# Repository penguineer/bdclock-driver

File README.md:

# Bulbdial Clock Driver board

> Driver Board for the bulbdial clock in [Netz39](https://www.netz39.de)

This is a driver board for the bulbdial clock built by [Yomin](https://github.com/Yomin) in [bdclock](https://github.com/Yomin/bdclock), which is in turn inspired by the bulbdial clock developed at [Evil Mad Scientist Laboratories](https://www.evilmadscientist.com/2009/a-bulbdial-clock/).

## Interface

The driver circuit operates independently and only needs to be fed data when the displayed values should change.

### Input

The circuit has three input controls `DATA`, `CLK` and `COMMIT`.

The data set contains of 3x8 data bits encoding the active LED for each of the three rows (where the order depends on how the rows are connected and only 0 to 11 lead to an illmuniated LED). Any number of bits can be sent, but only the last 24 bits will be stored in the registers.

The `DATA` is stored on the positive `CLK` edge. When all bits are loaded, the actual content is made visible to the drivers with a positive edge on `COMMIT`. For convenience, `CLK` and `COMMIT` can be driven together. In this case, the shift register's content is always one clock ahead of the storage register (see [SN74HC595 datasheet](https://www.ti.com/lit/ds/symlink/sn74hc595.pdf) p. 11).

### Output

The multiplexer is driven by an internal clock generater.

Each clock row is expected to have a common cathode, which will be multiplexed at the set switching frequency.

The line decoder selects one out of 12 LEDs to be active and expects the anodes of the clock LEDs to be connected to the matching output.

To switch a row off, select a value between 12 and 255, as these are ignored. The row will still be part of the multiplexing cycle.

## License

[MIT](LICENSE.txt) © 2023 Stefan Haun and contributors

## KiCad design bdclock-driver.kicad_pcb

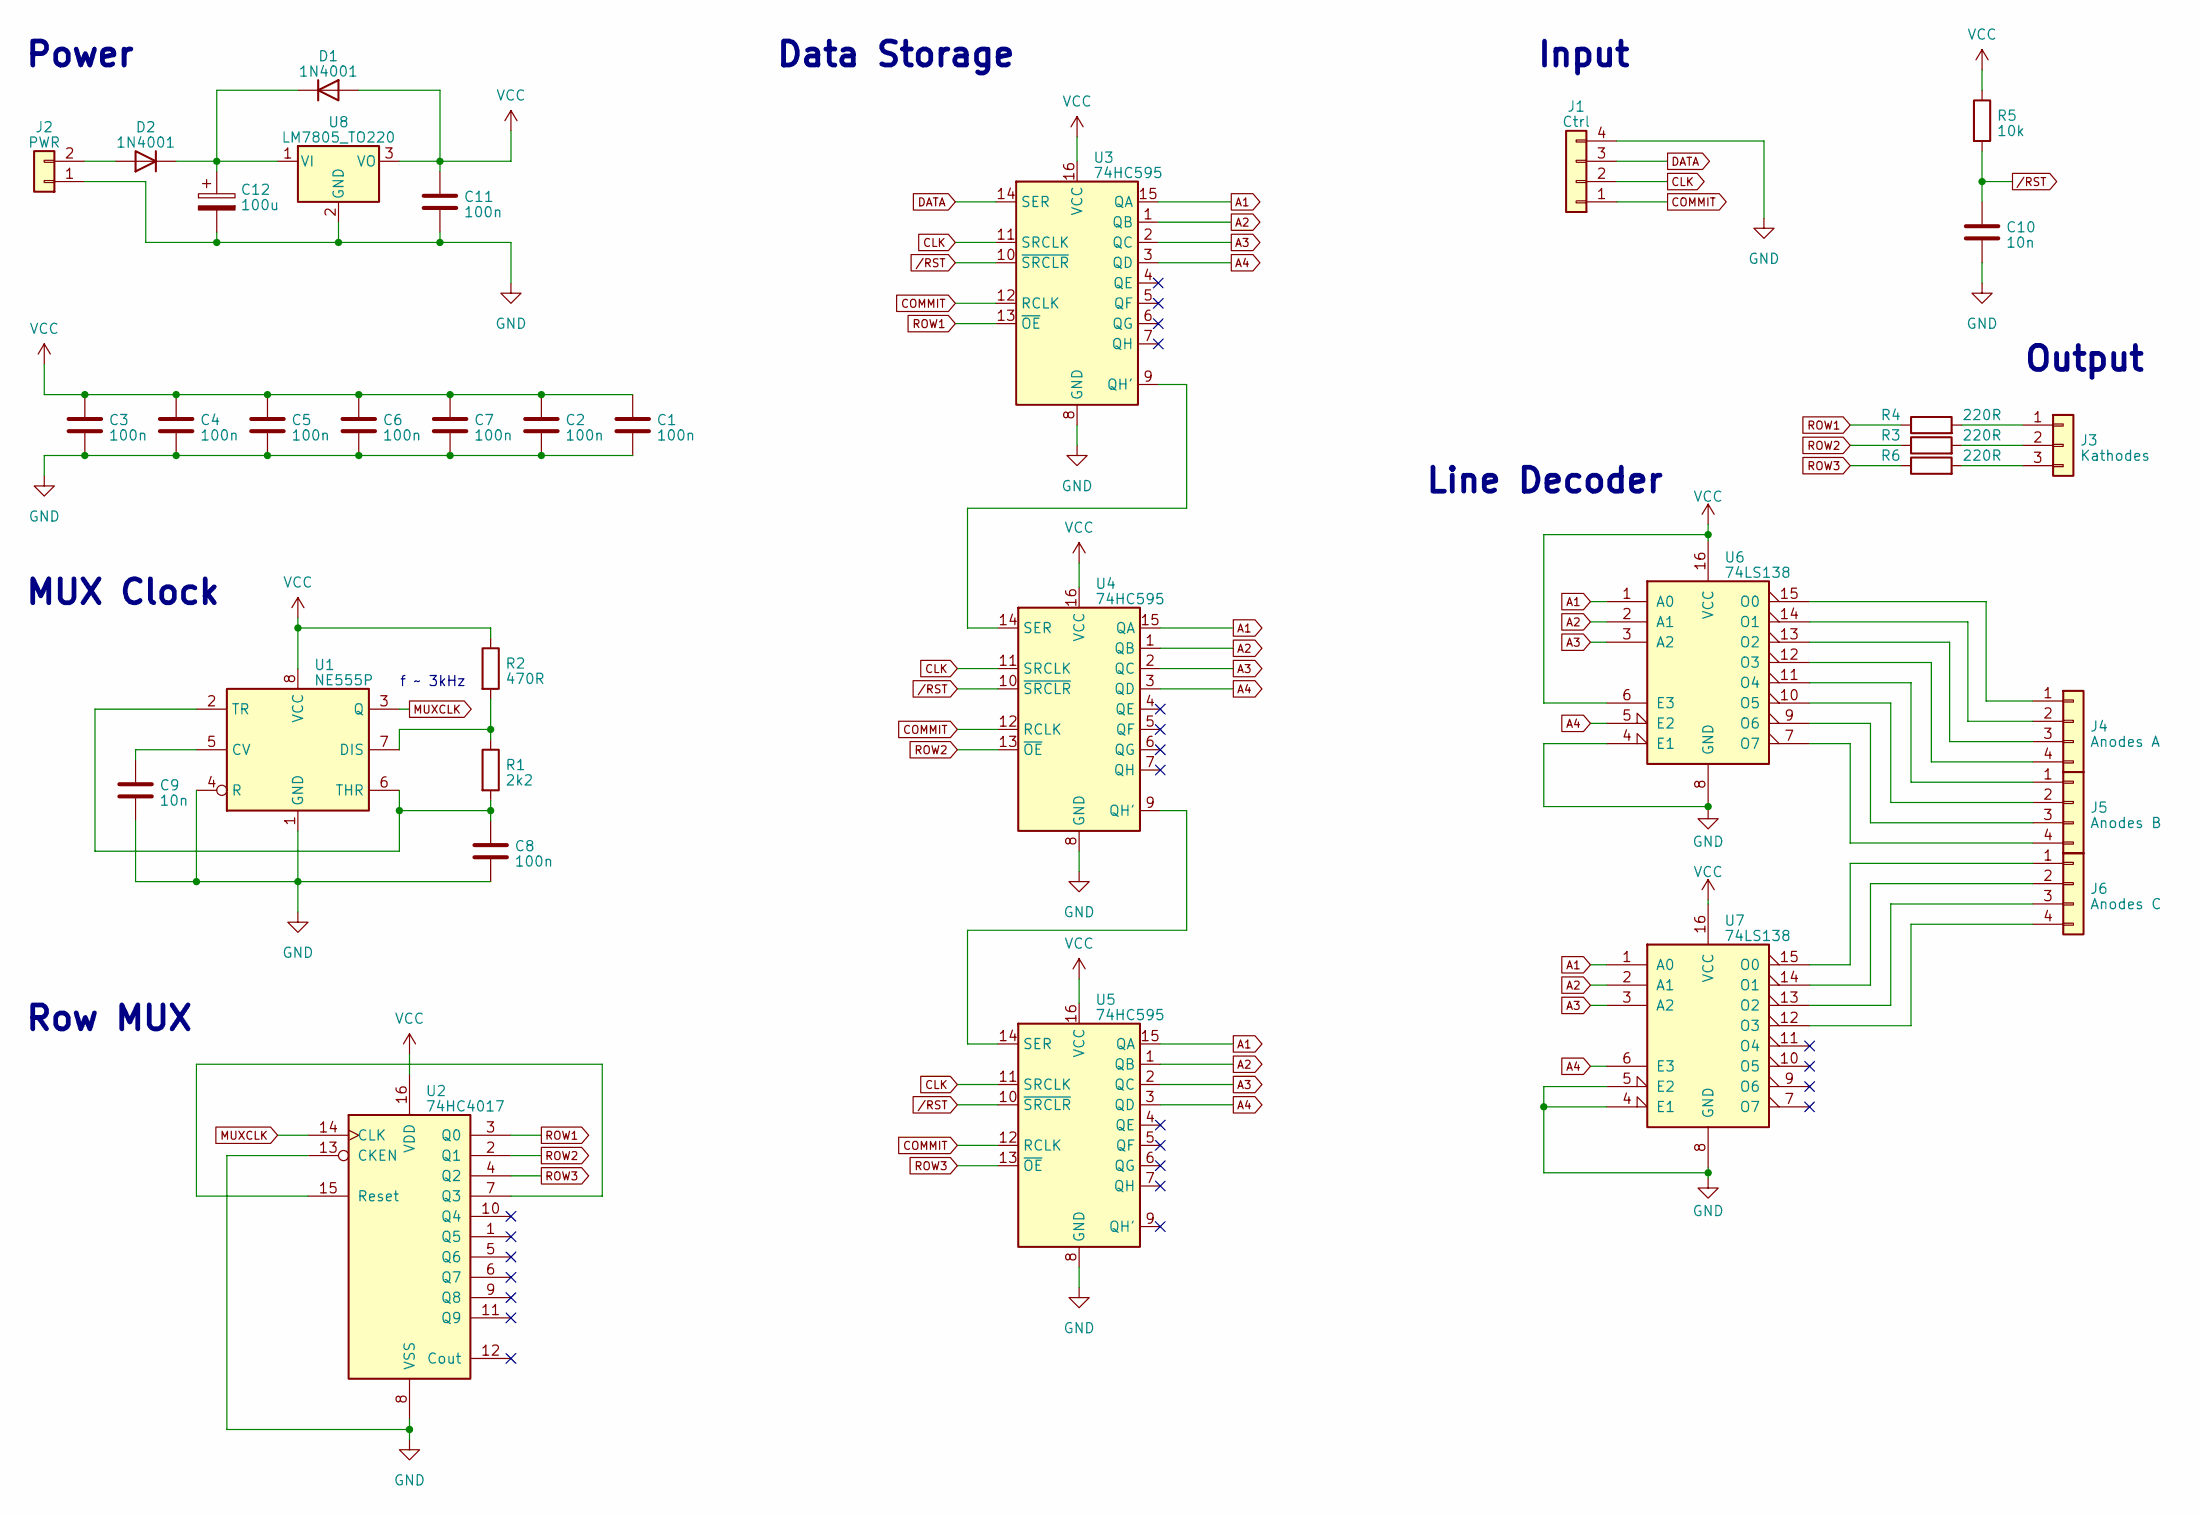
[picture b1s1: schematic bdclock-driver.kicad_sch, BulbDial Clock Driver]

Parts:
C1, C2, C3, C4, C5, C6, C7, C8, C11: 100n; C_Disc_D4.3mm_W1.9mm_P5.00mm
C9, C10: 10n; C_Disc_D4.3mm_W1.9mm_P5.00mm
C12: 100u; CP_Radial_D6.3mm_P2.50mm
D1, D2: 1N4001; D_DO-41_SOD81_P10.16mm_Horizontal
J1: Ctrl; PinSocket_1x04_P2.54mm_Vertical
J2: PWR; TerminalBlock_Altech_AK300-2_P5.00mm
J3: Kathodes; TerminalBlock_Altech_AK300-3_P5.00mm
J4: Anodes A; TerminalBlock_Altech_AK300-4_P5.00mm
J5: Anodes B; TerminalBlock_Altech_AK300-4_P5.00mm
J6: Anodes C; TerminalBlock_Altech_AK300-4_P5.00mm
R1: 2k2; R_Axial_DIN0207_L6.3mm_D2.5mm_P7.62mm_Horizontal
R2: 470R; R_Axial_DIN0207_L6.3mm_D2.5mm_P7.62mm_Horizontal
R3, R4, R6: 220R; R_Axial_DIN0207_L6.3mm_D2.5mm_P7.62mm_Horizontal
R5: 10k; R_Axial_DIN0207_L6.3mm_D2.5mm_P7.62mm_Horizontal
U1: NE555P; DIP-8_W7.62mm_Socket_LongPads
U2: 74HC4017; DIP-16_W7.62mm_Socket_LongPads
U3, U4, U5: 74HC595; DIP-16_W7.62mm_Socket_LongPads
U6, U7: 74LS138; DIP-16_W7.62mm_Socket_LongPads
U8: LM7805_TO220; TO-220-3_Vertical

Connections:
A1: U3.15 (QA), U4.15 (QA), U5.15 (QA), U6.1 (A0), U7.1 (A0)
A2: U3.1 (QB), U4.1 (QB), U5.1 (QB), U6.2 (A1), U7.2 (A1)
A3: U3.2 (QC), U4.2 (QC), U5.2 (QC), U6.3 (A2), U7.3 (A2)
A4: U3.3 (QD), U4.3 (QD), U5.3 (QD), U6.5 (E2), U7.6 (E3)
CLK: J1.2, U3.11 (SRCLK), U4.11 (SRCLK), U5.11 (SRCLK)
COMMIT: J1.1, U3.12 (RCLK), U4.12 (RCLK), U5.12 (RCLK)
DATA: J1.3, U3.14 (SER)
GND: C1.2, C2.2, C3.2, C4.2, C5.2, C6.2, C7.2, C8.2, C9.2, C10.2, C11.2, C12.2, J1.4, J2.1, U1.1 (GND), U1.4 (R), U2.8 (VSS), U2.13 (CKEN), U3.8 (GND), U4.8 (GND), U5.8 (GND), U6.4 (E1), U6.8 (GND), U7.4 (E1), U7.5 (E2), U7.8 (GND), U8.2 (GND)
MUXCLK: U1.3 (Q), U2.14 (CLK)
unnamed: C12.1, D1.1 (K), D2.1 (K), U8.1 (VI)
unnamed: D2.2 (A), J2.2
unnamed: J3.1, R4.2
unnamed: J3.2, R3.2
unnamed: J3.3, R6.2
unnamed: J4.1, U6.15 (O0)
unnamed: J4.2, U6.14 (O1)
unnamed: J4.3, U6.13 (O2)
unnamed: J4.4, U6.12 (O3)
unnamed: J5.1, U6.11 (O4)
unnamed: J5.2, U6.10 (O5)
unnamed: J5.3, U6.9 (O6)
unnamed: J5.4, U6.7 (O7)
unnamed: J6.1, U7.15 (O0)
unnamed: J6.2, U7.14 (O1)
unnamed: J6.3, U7.13 (O2)
unnamed: J6.4, U7.12 (O3)
unnamed: C9.1, U1.5 (CV)
unnamed: R1.1, R2.2, U1.7 (DIS)
unnamed: C8.1, R1.2, U1.2 (TR), U1.6 (THR)
unnamed: U2.7 (Q3), U2.15 (Reset)
unnamed: U3.9 (QH'), U4.14 (SER)
unnamed: U4.9 (QH'), U5.14 (SER)
ROW1: R4.1, U2.3 (Q0), U3.13 (~OE)
ROW2: R3.1, U2.2 (Q1), U4.13 (~OE)
ROW3: R6.1, U2.4 (Q2), U5.13 (~OE)
VCC: C1.1, C2.1, C3.1, C4.1, C5.1, C6.1, C7.1, C11.1, D1.2 (A), R2.1, R5.1, U1.8 (VCC), U2.16 (VDD), U3.16 (VCC), U4.16 (VCC), U5.16 (VCC), U6.6 (E3), U6.16 (VCC), U7.16 (VCC), U8.3 (VO)
/RST: C10.1, R5.2, U3.10 (~SRCLR), U4.10 (~SRCLR), U5.10 (~SRCLR)

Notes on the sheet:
MUX Clock
Row MUX
Input
Line Decoder
Output
f ~ 3kHz
Data Storage
Power

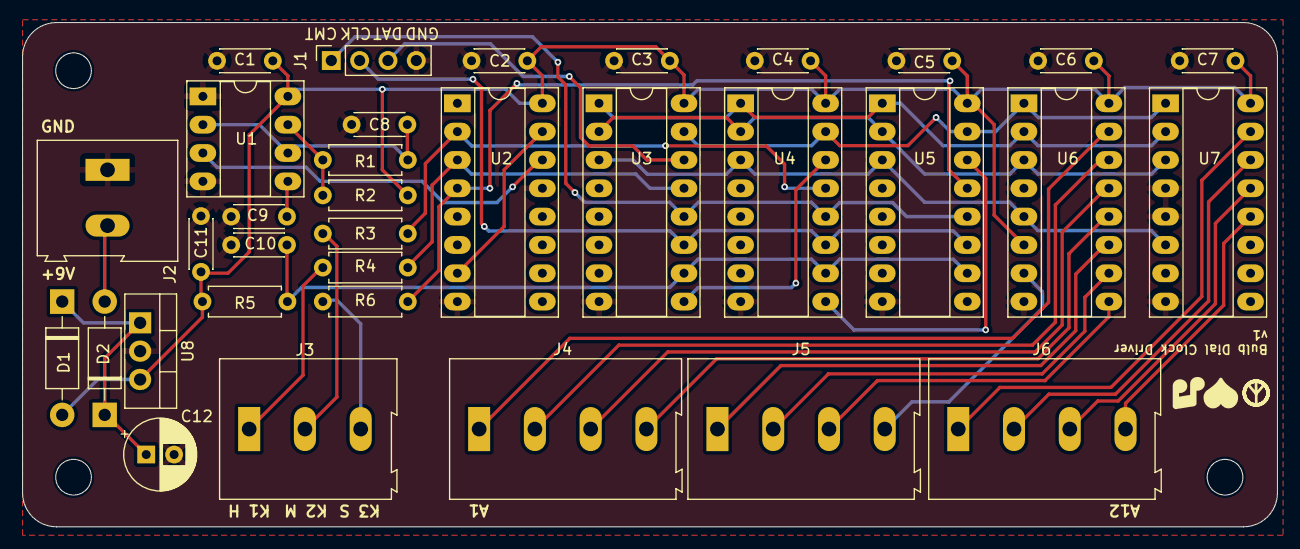
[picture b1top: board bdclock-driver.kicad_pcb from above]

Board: 2 copper layers, 112.5 x 45.2 mm, 34 parts (0 on the bottom side), 37 nets.

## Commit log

2023-05-16 :tada: Initial commit
2023-05-16 :page_facing_up: Add MIT license
2023-05-16 :money_with_wings: Add FUNDING infos
2023-05-16 :construction_worker: Add a release workflow
2023-05-16 :see_no_evil: Add gitignore for KiCad projects
2023-05-16 :tada: Add the KiCAD project
2023-05-23 :sparkles: Add schematic for the decoder/driver
2023-05-23 :memo: Add a short interface description
2023-05-25 :bug: Fix the wiring for the 595's cascading logic
2023-05-25 :memo: Adapt the input description to 595 cascading behaviour
2023-05-25 :wrench: Assign missing footprints
2023-05-25 :sparkles: Add PCB layout draft
2023-08-15 :hammer: Improve PCB layout
2023-08-20 :art: Finalize the PCB layout
2023-08-20 :art: Geographical renumeration of all components
2023-11-21 :art: Place JLCPCB serial number marker and add GND to data connector
